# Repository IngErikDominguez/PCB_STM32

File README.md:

# PCB_STM32
PCB_STM32 

El PCB de Stm32 se comienza con el objetivo de sustituir el arduino nano, por un desarrollo generado aquí. El objetivo del microcontrolador, será embeber la comunicación serial con los dispositivos ccTalk, monitorear sensores que se empiecen a implementar, como lo son: sensor de corriente, voltaje, temperatura y tener una comunicación mas transparente con un software de PC o Raspberry por comunicación serial

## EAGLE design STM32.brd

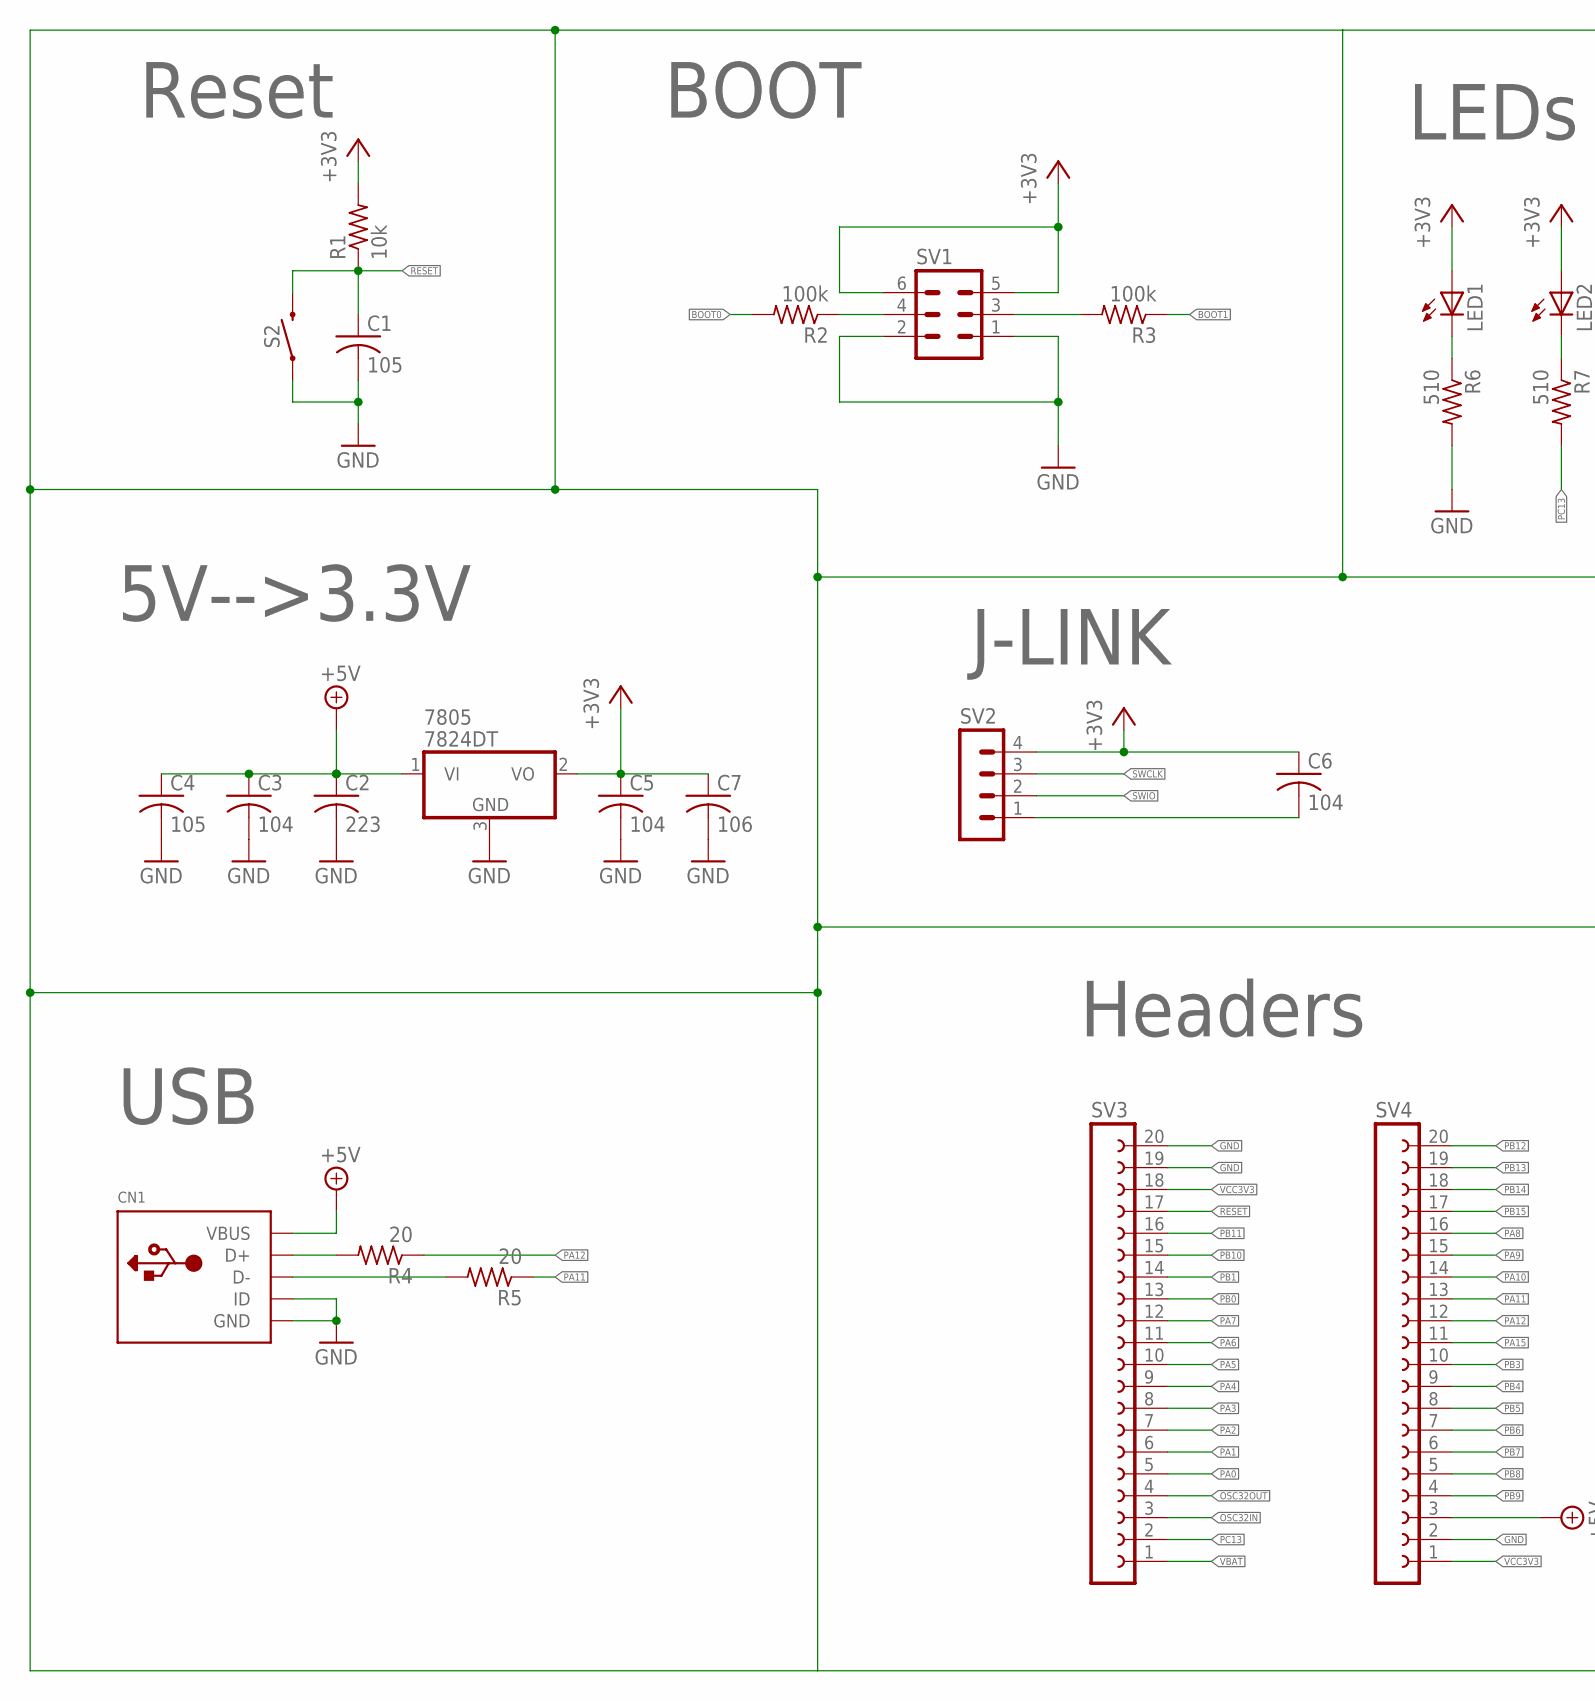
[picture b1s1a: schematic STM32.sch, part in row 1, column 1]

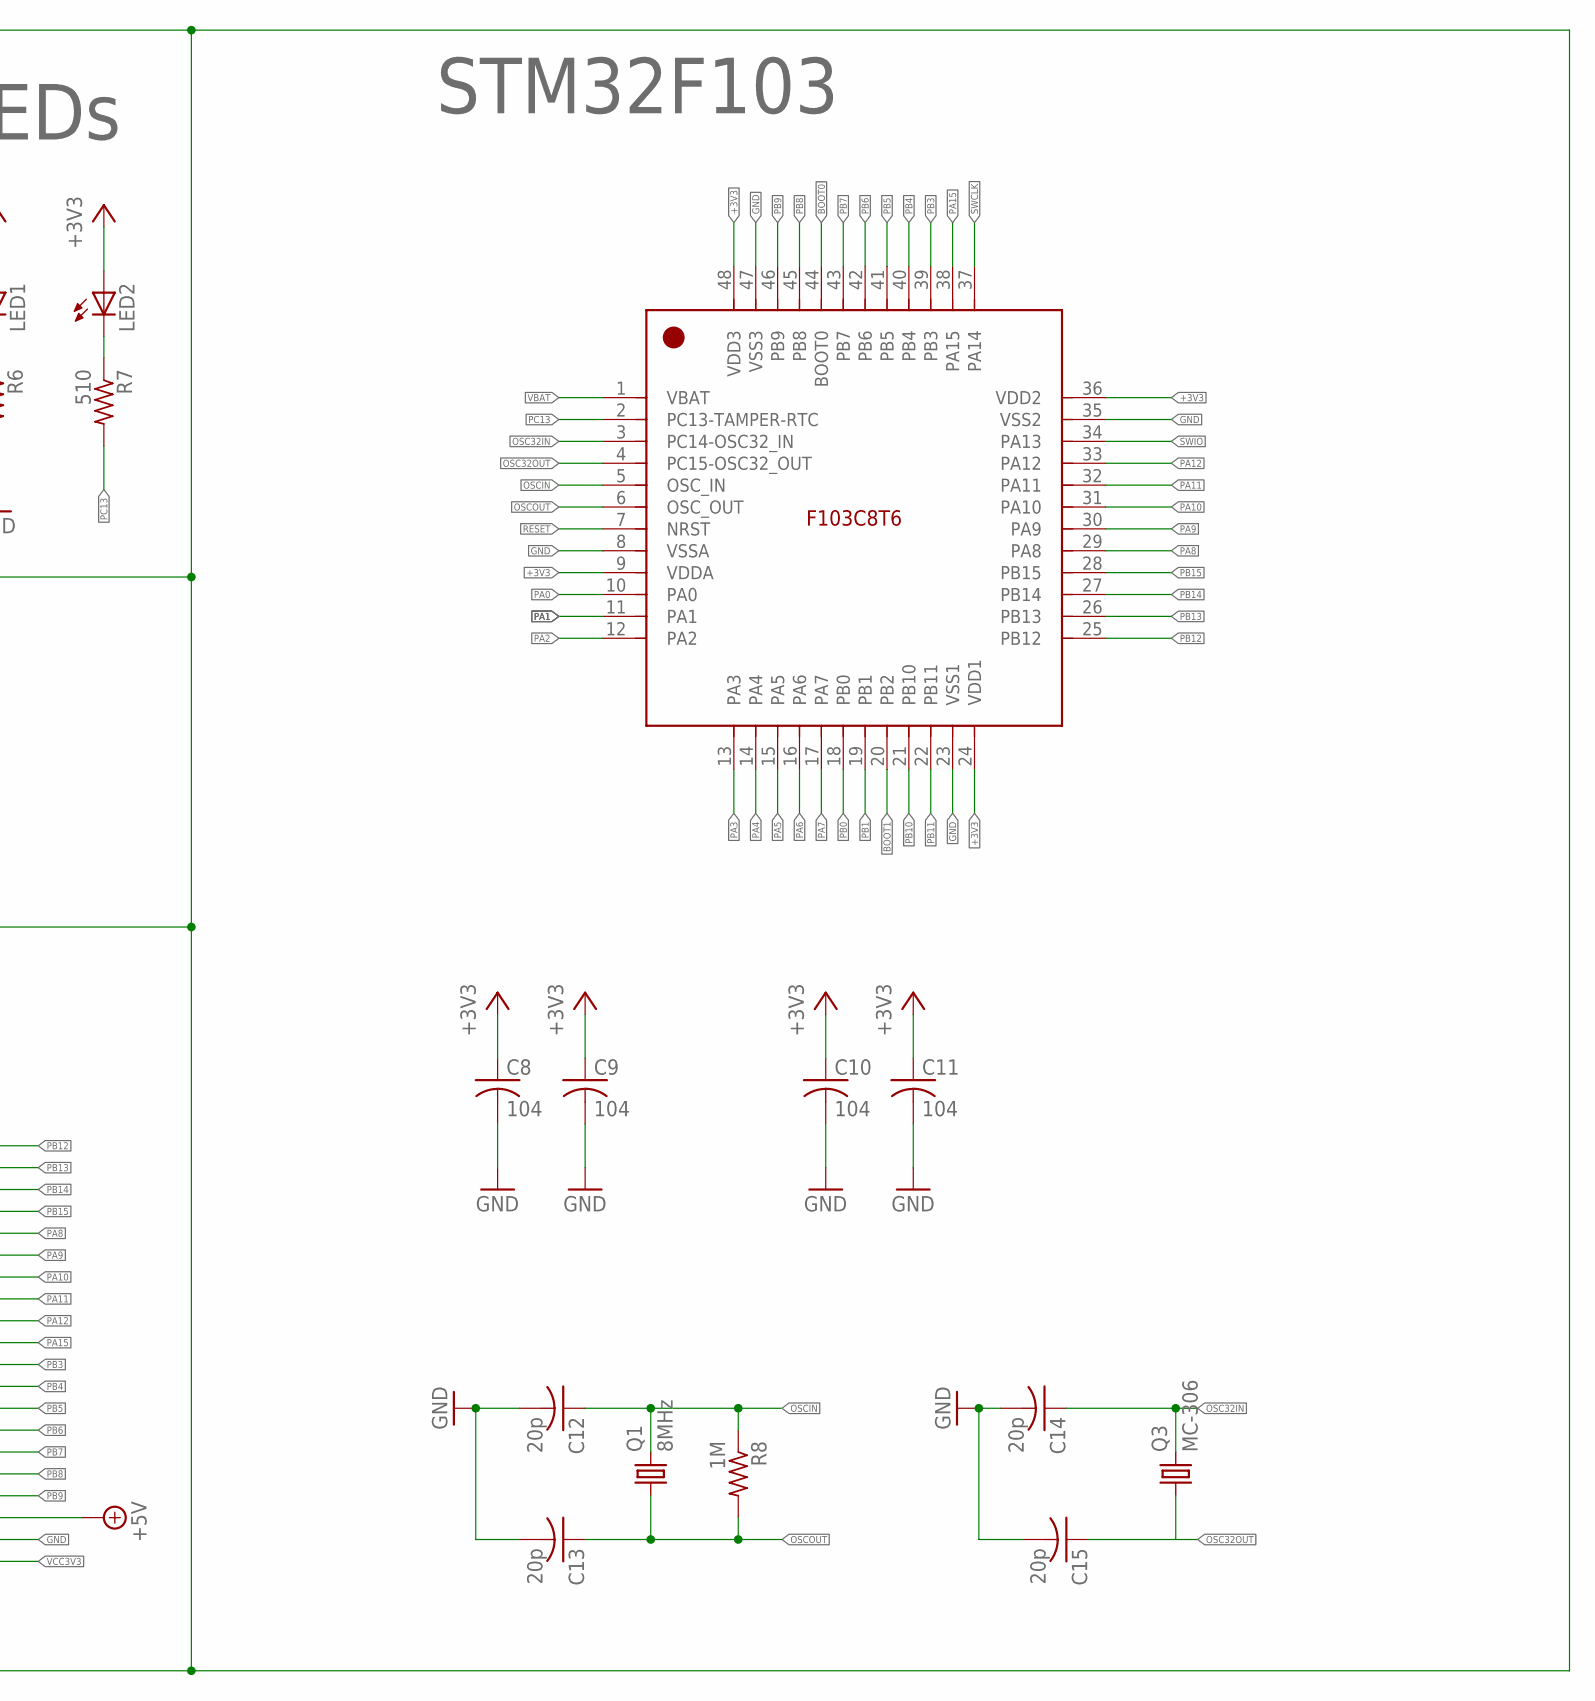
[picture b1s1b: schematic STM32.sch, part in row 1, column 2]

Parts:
7805: 7824DT; TO252
C1: 105; C0603
C2: 223; C0603
C3, C5, C6, C8, C9, C10, C11: 104; C0603
C4: 105; C0805
C7: 106; C0805
C12, C13, C14, C15: 20p; C0603
CN1: USBMINIB; USB-MINIB
LED1, LED2: LEDCHIPLED_0805; CHIPLED_0805
Q1: 8MHz; HC49U70
Q3: MC-306
R1: 10k; R0603
R2, R3: 100k; R0603
R4, R5: 20; R0603
R6, R7: 510; R0603
R8: 1M; R0603
S2: MOMENTARY-SWITCH-SPST-SMD-5.2-REDUNDANT; TACTILE_SWITCH_SMD_5.2MM
SV1: MA03-2
SV2: MA04-1
SV3, SV4: FE20-1; FE20
U$1: STM32F103C8T6; LQFP48_7X7MM_0.5MMPP

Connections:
+3V3: 7805.2 (VO), C5.1, C6.1, C7.1, C8.1, C9.1, C10.1, C11.1, LED1.A, LED2.A, R1.2, SV1.5, SV1.6, SV2.4, U$1.9 (VDDA), U$1.24 (VDD1), U$1.36 (VDD2), U$1.48 (VDD3)
+5V: 7805.1 (VI), C2.1, C3.1, C4.1, CN1.VBUS, SV4.3
BOOT0: R2.2, U$1.44 (BOOT0)
BOOT1: R3.1, U$1.20 (PB2)
GND: 7805.3 (GND), C1.2, C2.2, C3.2, C4.2, C5.2, C7.2, C8.2, C9.2, C10.2, C11.2, C12.2, C13.2, C14.2, C15.2, CN1.GND, CN1.ID, R6.2, S2.1, S2.2 (1), SV1.1, SV1.2, SV3.19, SV3.20, SV4.2, U$1.8 (VSSA), U$1.23 (VSS1), U$1.35 (VSS2), U$1.47 (VSS3)
unnamed: R2.1, SV1.4
unnamed: R3.2, SV1.3
unnamed: LED1.C, R6.1
unnamed: CN1.D+, R4.2
unnamed: CN1.D-, R5.2
unnamed: LED2.C, R7.1
unnamed: C6.2, SV2.1
OSC32IN: C14.1, Q3.4 (2), SV3.3, U$1.3 (PC14-OSC32_IN)
OSC32OUT: C15.1, Q3.1, SV3.4, U$1.4 (PC15-OSC32_OUT)
OSCIN: C12.1, Q1.2, R8.1, U$1.5 (OSC_IN)
OSCOUT: C13.1, Q1.1, R8.2, U$1.6 (OSC_OUT)
PA0: SV3.5, U$1.10 (PA0)
PA1: SV3.6, U$1.11 (PA1)
PA2: SV3.7, U$1.12 (PA2)
PA3: SV3.8, U$1.13 (PA3)
PA4: SV3.9, U$1.14 (PA4)
PA5: SV3.10, U$1.15 (PA5)
PA6: SV3.11, U$1.16 (PA6)
PA7: SV3.12, U$1.17 (PA7)
PA8: SV4.16, U$1.29 (PA8)
PA9: SV4.15, U$1.30 (PA9)
PA10: SV4.14, U$1.31 (PA10)
PA11: R5.1, SV4.13, U$1.32 (PA11)
PA12: R4.1, SV4.12, U$1.33 (PA12)
PA15: SV4.11, U$1.38 (PA15)
PB0: SV3.13, U$1.18 (PB0)
PB1: SV3.14, U$1.19 (PB1)
PB3: SV4.10, U$1.39 (PB3)
PB4: SV4.9, U$1.40 (PB4)
PB5: SV4.8, U$1.41 (PB5)
PB6: SV4.7, U$1.42 (PB6)
PB7: SV4.6, U$1.43 (PB7)
PB8: SV4.5, U$1.45 (PB8)
PB9: SV4.4, U$1.46 (PB9)
PB10: SV3.15, U$1.21 (PB10)
PB11: SV3.16, U$1.22 (PB11)
PB12: SV4.20, U$1.25 (PB12)
PB13: SV4.19, U$1.26 (PB13)
PB14: SV4.18, U$1.27 (PB14)
PB15: SV4.17, U$1.28 (PB15)
PC13: R7.2, SV3.2, U$1.2 (PC13-TAMPER-RTC)
RESET: C1.1, R1.1, S2.3 (2), S2.4 (2), SV3.17, U$1.7 (NRST)
SWCLK: SV2.3, U$1.37 (PA14)
SWIO: SV2.2, U$1.34 (PA13)
VBAT: SV3.1, U$1.1 (VBAT)
VCC3V3: SV3.18, SV4.1

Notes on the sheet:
Reset
BOOT
5V-->3.3V
USB
J-LINK
STM32F103
Headers
LEDs

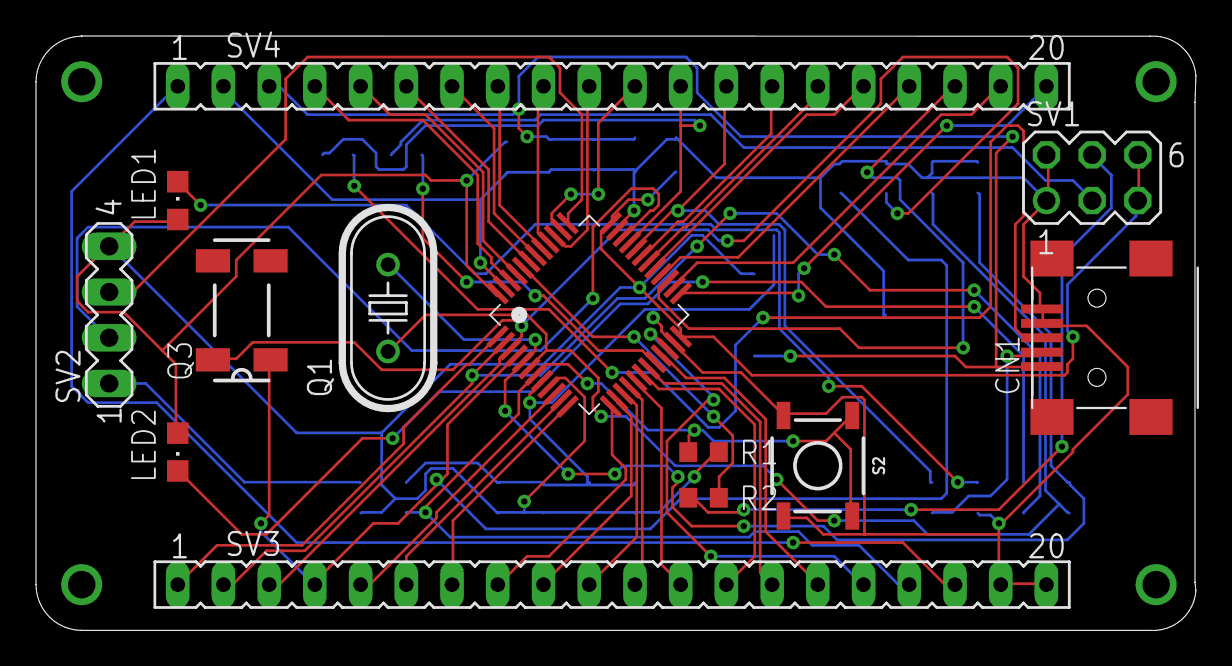
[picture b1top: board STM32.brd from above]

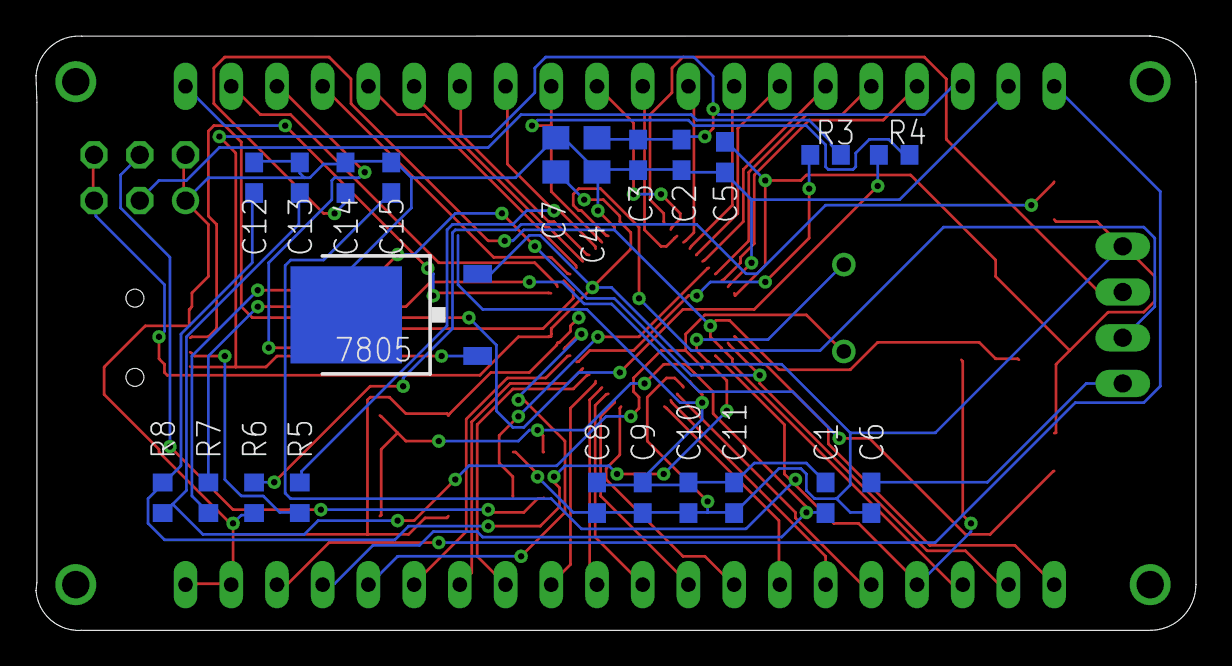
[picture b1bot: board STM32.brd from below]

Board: 2 copper layers, 64.4 x 33.0 mm, 35 parts (22 on the bottom side), 51 nets.

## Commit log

2019-03-07 V1.0
    Primer esquematico con E/S disponibles para prototipado
2019-03-08 V1.0
    Se termina el primer ruteado

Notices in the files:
parts and their libraries:
SparkFun-Switches: Licensing: Creative Commons ShareAlike 4.0 International - https://creativecommons.org/licenses/by-sa/4.0
